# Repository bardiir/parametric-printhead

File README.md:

# parametric-printhead
Build of a parametric printhead encapsulation for the CTC Bizer Dual that replaces one extruder with a cooling assembly and makes it possible to fast-swap the printhead by using ethernet connectors.

## What this is about?
I've experienced a lot of cable breaks with the printhead of my CTC machine, most of them within the Thermocouple wires as they are not meant for a lot of movement. So I decided to replace the wires that run all the way down to the mainboard with a more flexible solution, ethernet cable. This offers me a possibility to easily exchange the printhead too as the connection is just clipped and the printhead only is fixed with two screws on the carriage. If the cable fails again it's not just a 10 seconds fix and a 1€ cost for the cable instead of having to open up the whole cable structure, dig out the failed cable and replace it complete with the thermocouple. They are not prohibitively expensive but they do cost more in the long run to replace.

## Mk1
I'm using Ethernet patch connector extension wires (http://amzn.to/2nQmoxb), cut them open and used the cables to connect the fan, extruder and heating element on the printhead with one set of these as well as every connection going to the mainboard with another set of these. In between the two ethernet sockets I'm then using 0,5m patch cables. I've matched everything in red and white to differentiate between the sockets but that is purely cosmetics.

## Mk2
This has been changed:
- Better air exhaust design, this was just a first proof of conecpt to see if everything works, the air outlet of Mk1 mainly cools the nozzle not the extruded filament, this is bad
- Custom PCB, using the patch extensions was just quick workaround
- Added some fuses - polyfuses for the heater wires going through ethernet so if one of the connections gets cut it doesn't result in an overload on the remaining one as well as an additional burn fuse on the PCB to prevent the heater current to leave safe levels alltogether

There also have been plans to do these:
- Have the Thermocouple read at the printhead not back at the mainboard, shield SPI bus from EMI noise  
-> Actually this did result in very bad behavior in all Tests, the error margin for the Thermocouple is low enough to work for this case anyway. However it is a little bit depending on the environment temperature this way which is actually good in this case as it errs to higher temperatures measured in hotter environments which lowers the print temperature and actually levels out the error caused by the environment in the first place. But this is only 1-2°C anyway.

- Have an expansion modifier for annnealing the part. Ideally this part, as it is in direct contact with hot elements of the printhead should be annealed to increase it's temperature stability, this however does cause some warping (see this video: https://www.youtube.com/watch?v=CZX8eHC7fws&t=141s), there should be a modifier to take care of this  
-> Currently using aluminium tape to shield the part, works like a charm, no annealing necessary

- Use nuts to screw fan duct and exhaust together  
-> It's now one part anyway, no need to screw it together, but maybe I'll create a Mk3 version that is screwed if someone can't or doesn't want to print big support structures.

## Future plans
- Make Exhaust clip-on and easily exchangeable to cater for various nozzle heights without changeing the whole printhead and to make it printable as an extra part, ideally without any supports

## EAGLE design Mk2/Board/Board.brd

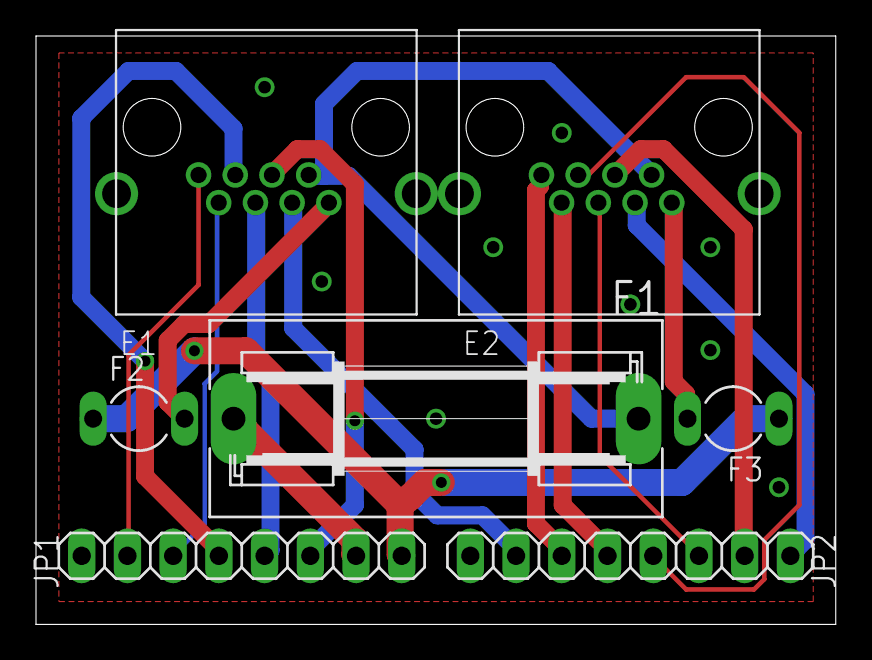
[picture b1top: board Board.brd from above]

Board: 2 copper layers, 44.4 x 32.7 mm, 7 parts (0 on the bottom side), 18 nets.

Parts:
E1, E2: RJ45
F1: 2A; SH22,5A
F2, F3: 1A; POLYFUSE
JP1, JP2: 1X08

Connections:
GND: E1.S@1, E1.S@2, E2.S@1, E2.S@2, JP1.8, JP2.8
unnamed: E1.8, F2.2
unnamed: E2.8, F3.2
unnamed: E1.7, E2.7, F1.1
unnamed: F2.1, F3.1, JP1.1
unnamed: F1.2, JP1.2
unnamed: E1.1, JP1.7
unnamed: E1.2, JP1.6
unnamed: E1.3, JP1.5
unnamed: E1.4, JP1.4
unnamed: E1.5, JP1.3
unnamed: E1.6, JP2.7
unnamed: E2.1, JP2.6
unnamed: E2.2, JP2.5
unnamed: E2.3, JP2.4
unnamed: E2.4, JP2.3
unnamed: E2.5, JP2.2
unnamed: E2.6, JP2.1

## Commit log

2017-03-31 ignore 3d printing generated files
2017-04-01 added cable box
2017-04-01 connect supports to save printtime by generating less perimeters
2017-04-01 add ethernet connectors connection definition
2017-04-01 mightyboard schematic
2017-04-01 testprint, adjusted measurements with tolerances and thicker walls for more stability
2017-04-01 test print, adjusted values
2017-04-01 made it possible to print singular parts, testprints, finetuning values
2017-04-01 easier render selection for different parts
2017-04-02 opened up ethernet sockets to insert ethernet port with cables attached and created printer side plate
2017-04-02 ignore mac files
2017-04-02 add filament guide to printer plate
2017-04-03 finalized printhead 1, testprints for #2 started, adjusted values and added a calibration notes file to keep different measurements for the printheads
2017-04-03 having the MAX6675 at the print head is not a viable option, the SPI bus is easily interrupted by the extruders stepper motor control nearby, creating noise in the temperature reads and sometimes eve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
2017-04-03 added some more description
2017-04-03 restructured folders
2017-04-03 Keine Meldung
2017-04-03 too late…
2017-04-06 cleanup exhaust, generate cutout to prevent sagging exhaust and make fitting over an installed nozzle easier
2017-04-06 improve airflow by increasing lower cutout diameter on the exhaust
2017-04-07 measurements for second printhead
2017-05-13 changed parameters after testprints
2017-05-13 filament guide plate for the bowden tube to the printhead
2017-05-13 ethernet board for Mk2 Printhead
2017-05-13 moved the appropiate files to the Mk1 Printhead design, Mk2 will use a different cable layout and different parameters for the design
2017-05-13 board design
2017-06-07 board finalization
2017-06-07 printhead Mk2 initial version
2017-06-08 boards a a bit wider, also they do have solder joints that are not flush *facepalm*
2017-06-08 opening not always towards nozzle, enlongening cutout cube to make wall break every time
2017-06-08 clearance issue with aluminium printhead sled
2017-06-08 enlarge cutout in cable chamber lid for top plate to make space for the moved board
2017-06-09 wall thickness changed to 1.6 to better match the 0.4 nozzle currently installed, also added some manually created support as a modifier
2017-06-09 give support block a bit more space so it doesnt adhere to the exhaust when printing
2017-12-19 Create LICENSE
